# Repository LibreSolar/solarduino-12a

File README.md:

# Solarduino_12A
12A MPPT solar charge controller based on Arduino

Features: 
- 12A MPPT charger
- 55V max PV input
- 12V or 24V battery output
- Arduino-compatible (ATmega 328P used)
- Expandable via break-out of unused ports to standard 2.54 pin-pitch headers (e.g. used for display, communication like CAN/RS485, etc.)

Built-in protection:
- Overvoltage
- Undervoltage
- Overcurrent
- PV short circuit
- PV reverse polarity (for max. module open circuit voltage of around 40V)
- Battery reverse polarity (destructive, fuse is blown)

# Roadmap
- This is the new version of the charge controller. First PCB was sent to production beginning of May 2016. First test results end of May expected.

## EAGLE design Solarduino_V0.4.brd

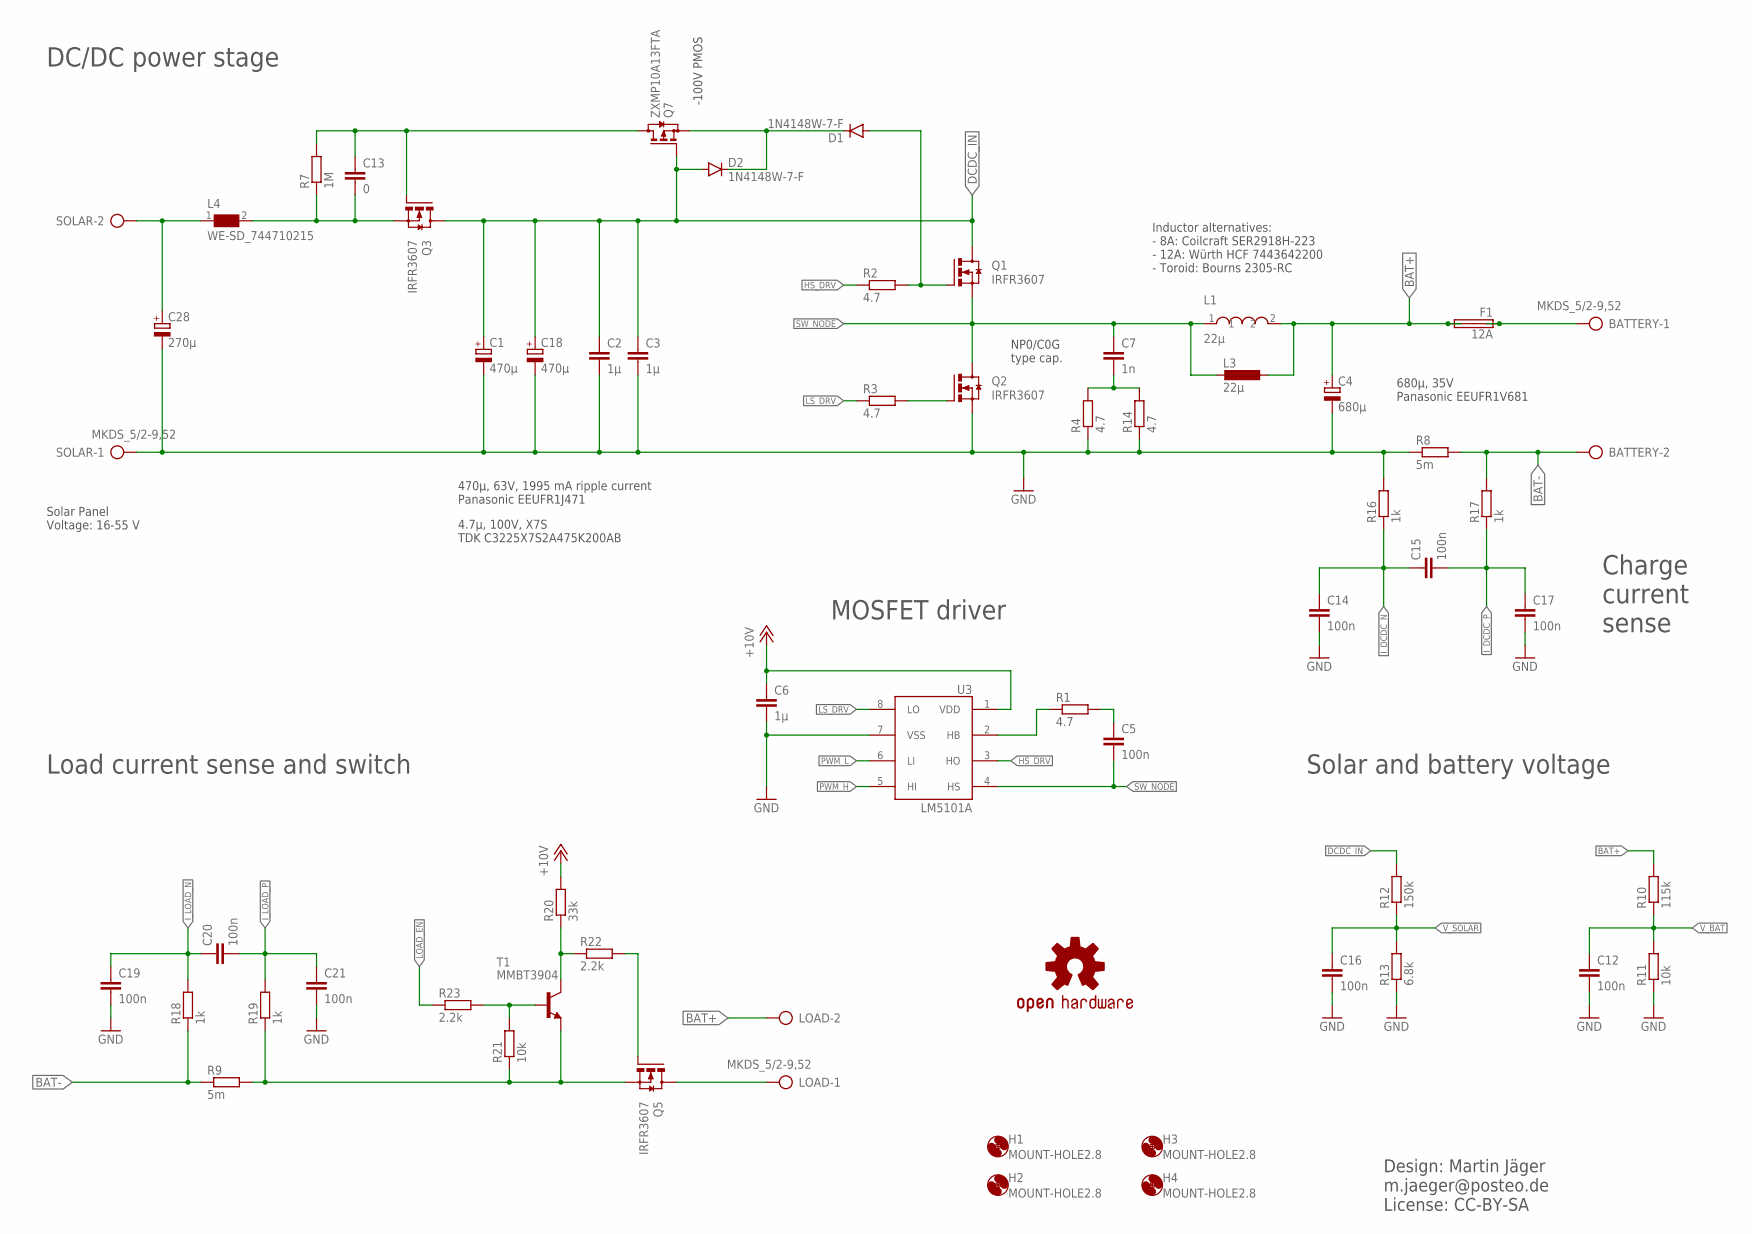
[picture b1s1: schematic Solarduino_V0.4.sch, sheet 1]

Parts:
BATTERY: MKDS_5/2-9,52; MKDS_5/2-952
C1, C18: 470µ; E5-13; MPN EEUFR1J331B
C2, C3: 1µ; C0805; MPN C3225X7S2A475K200AB
C4: 680µ; E5-10,5; MPN EEUFR1E821B
C5, C12, C14, C15, C16, C17, C19, C20, C21: 100n; C0603; MPN 08055C104KAT2A
C6: 1µ; C0603; MPN 08055C104KAT2A
C7: 1n; C0805; MPN 08055C104KAT2A
C13: 0; C0603; MPN 08055C104KAT2A
C28: 270µ; E5-10,5; MPN EEUFR1E821B
D1, D2: 1N4148W-7-F; SOD-123
F1: 12A; BLADE_FUSE_STD
H1, H2, H3, H4: MOUNT-HOLE2.8; 2,8
L1: 22µ; WE-HCF_2818_7443643300; MPN SER2918H-223KL
L3: 22µ; L-BOURNS-2300-H
L4: WE-SD_744710215
LOAD: MKDS_5/2-9,52; MKDS_5/2-952
N1: OSHW-LOGOM; OSHW-LOGO-M
Q1, Q2, Q3, Q5: IRFR3607; DPAK
Q7: ZXMP10A13FTA; SOT23; MPN BSS84-7-F
R1: 4.7; R0805; MPN CR0805-FX-1001ELF
R2, R3: 4.7; R0805; MPN CR0805-FX-1004ELF.
R4, R14: 4.7; R1206; MPN CRM2010-JW-2R2ELF
R7: 1M; R0603; MPN CR0805-FX-1004ELF.
R8, R9: 5m; R2512; MPN CRF2512-FX-R005ELF
R10: 115k; R0603; MPN ERA6AEB104V
R11: 10k; R0603; MPN ERA6AEB682V
R12: 150k; R0603; MPN ERA6AEB104V
R13: 6.8k; R0603; MPN ERA6AEB104V
R16, R17, R18, R19: 1k; R0603; MPN CRM2010-JW-2R2ELF
R20: 33k; R0603; MPN CRM2010-JW-2R2ELF
R21: 10k; R0603; MPN CRM2010-JW-2R2ELF
R22, R23: 2.2k; R0603; MPN CR0805-FX-1004ELF.
SOLAR: MKDS_5/2-9,52; MKDS_5/2-952
T1: MMBT3904; SOT23-BEC
U3: LM5101A; SOIC-8-N

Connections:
+10V: C6.1, R20.2, U3.1 (VDD); also elsewhere on the board
BAT+: C4.+, F1.P$3 (2A), F1.P$4 (2B), L1.2, L3.P$1 (1), LOAD.2, R10.2; also elsewhere on the board
BAT-: BATTERY.2, R8.2, R9.1, R17.2, R18.1
DCDC_IN: C1.+, C2.1, C3.1, C18.+, D2.A, Q1.4 (D), Q3.4 (D), Q7.1 (G), R12.2
FUSE+: BATTERY.1, F1.P$1 (1A), F1.P$2 (1B)
GND: C1.-, C2.2, C3.2, C4.-, C6.2, C12.2, C14.2, C16.2, C17.2, C18.-, C19.2, C21.2, C28.-, Q2.3 (S), R4.1, R8.1, R11.1, R13.1, R14.1, R16.2, SOLAR.1, U3.7 (VSS); also elsewhere on the board
HS_DRV: R2.1, U3.3 (HO)
I_DCDC_N: C14.1, C15.1, R16.1; also elsewhere on the board
I_DCDC_P: C15.2, C17.1, R17.1; also elsewhere on the board
I_LOAD_N: C19.1, C20.1, R18.2; also elsewhere on the board
I_LOAD_P: C20.2, C21.1, R19.2; also elsewhere on the board
LC_OUT: C13.2, L4.2, Q3.3 (S), R7.1
LOAD-: LOAD.1, Q5.4 (D)
LOAD_EN: R23.1; also elsewhere on the board
LOAD_G: Q5.1 (G), R22.2
LS_DRV: R3.1, U3.8 (LO)
unnamed: R1.1, U3.2 (HB)
unnamed: C5.1, R1.2
unnamed: D1.A, Q1.1 (G), R2.2
unnamed: Q5.3 (S), R9.2, R19.1, R21.1, T1.E
unnamed: C13.1, Q3.1 (G), Q7.3 (D), R7.2
unnamed: Q2.1 (G), R3.2
unnamed: D1.C, D2.C, Q7.2 (S)
unnamed: R20.1, R22.1, T1.C
unnamed: C7.2, R4.2, R14.2
unnamed: R21.2, R23.2, T1.B
PWM_H: U3.5 (HI); also elsewhere on the board
PWM_L: U3.6 (LI); also elsewhere on the board
SOLAR+: C28.+, L4.1, SOLAR.2
SW_NODE: C5.2, C7.1, L1.1, L3.P$2 (2), Q1.3 (S), Q2.4 (D), U3.4 (HS)
V_BAT: C12.1, R10.1, R11.2; also elsewhere on the board
V_SOLAR: C16.1, R12.1, R13.2; also elsewhere on the board

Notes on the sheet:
470µ, 63V, 1995 mA ripple current Panasonic EEUFR1J471
680µ, 35V Panasonic EEUFR1V681
Solar Panel Voltage: 16-55 V
Design: Martin Jäger m.jaeger@posteo.de License: CC-BY-SA
DC/DC power stage
4.7µ, 100V, X7S TDK C3225X7S2A475K200AB
Inductor alternatives: - 8A: Coilcraft SER2918H-223 - 12A: Würth HCF 7443642200 - Toroid: Bourns 2305-RC
-100V PMOS
NP0/C0G type cap.
Load current sense and switch
Charge current sense
MOSFET driver
Solar and battery voltage

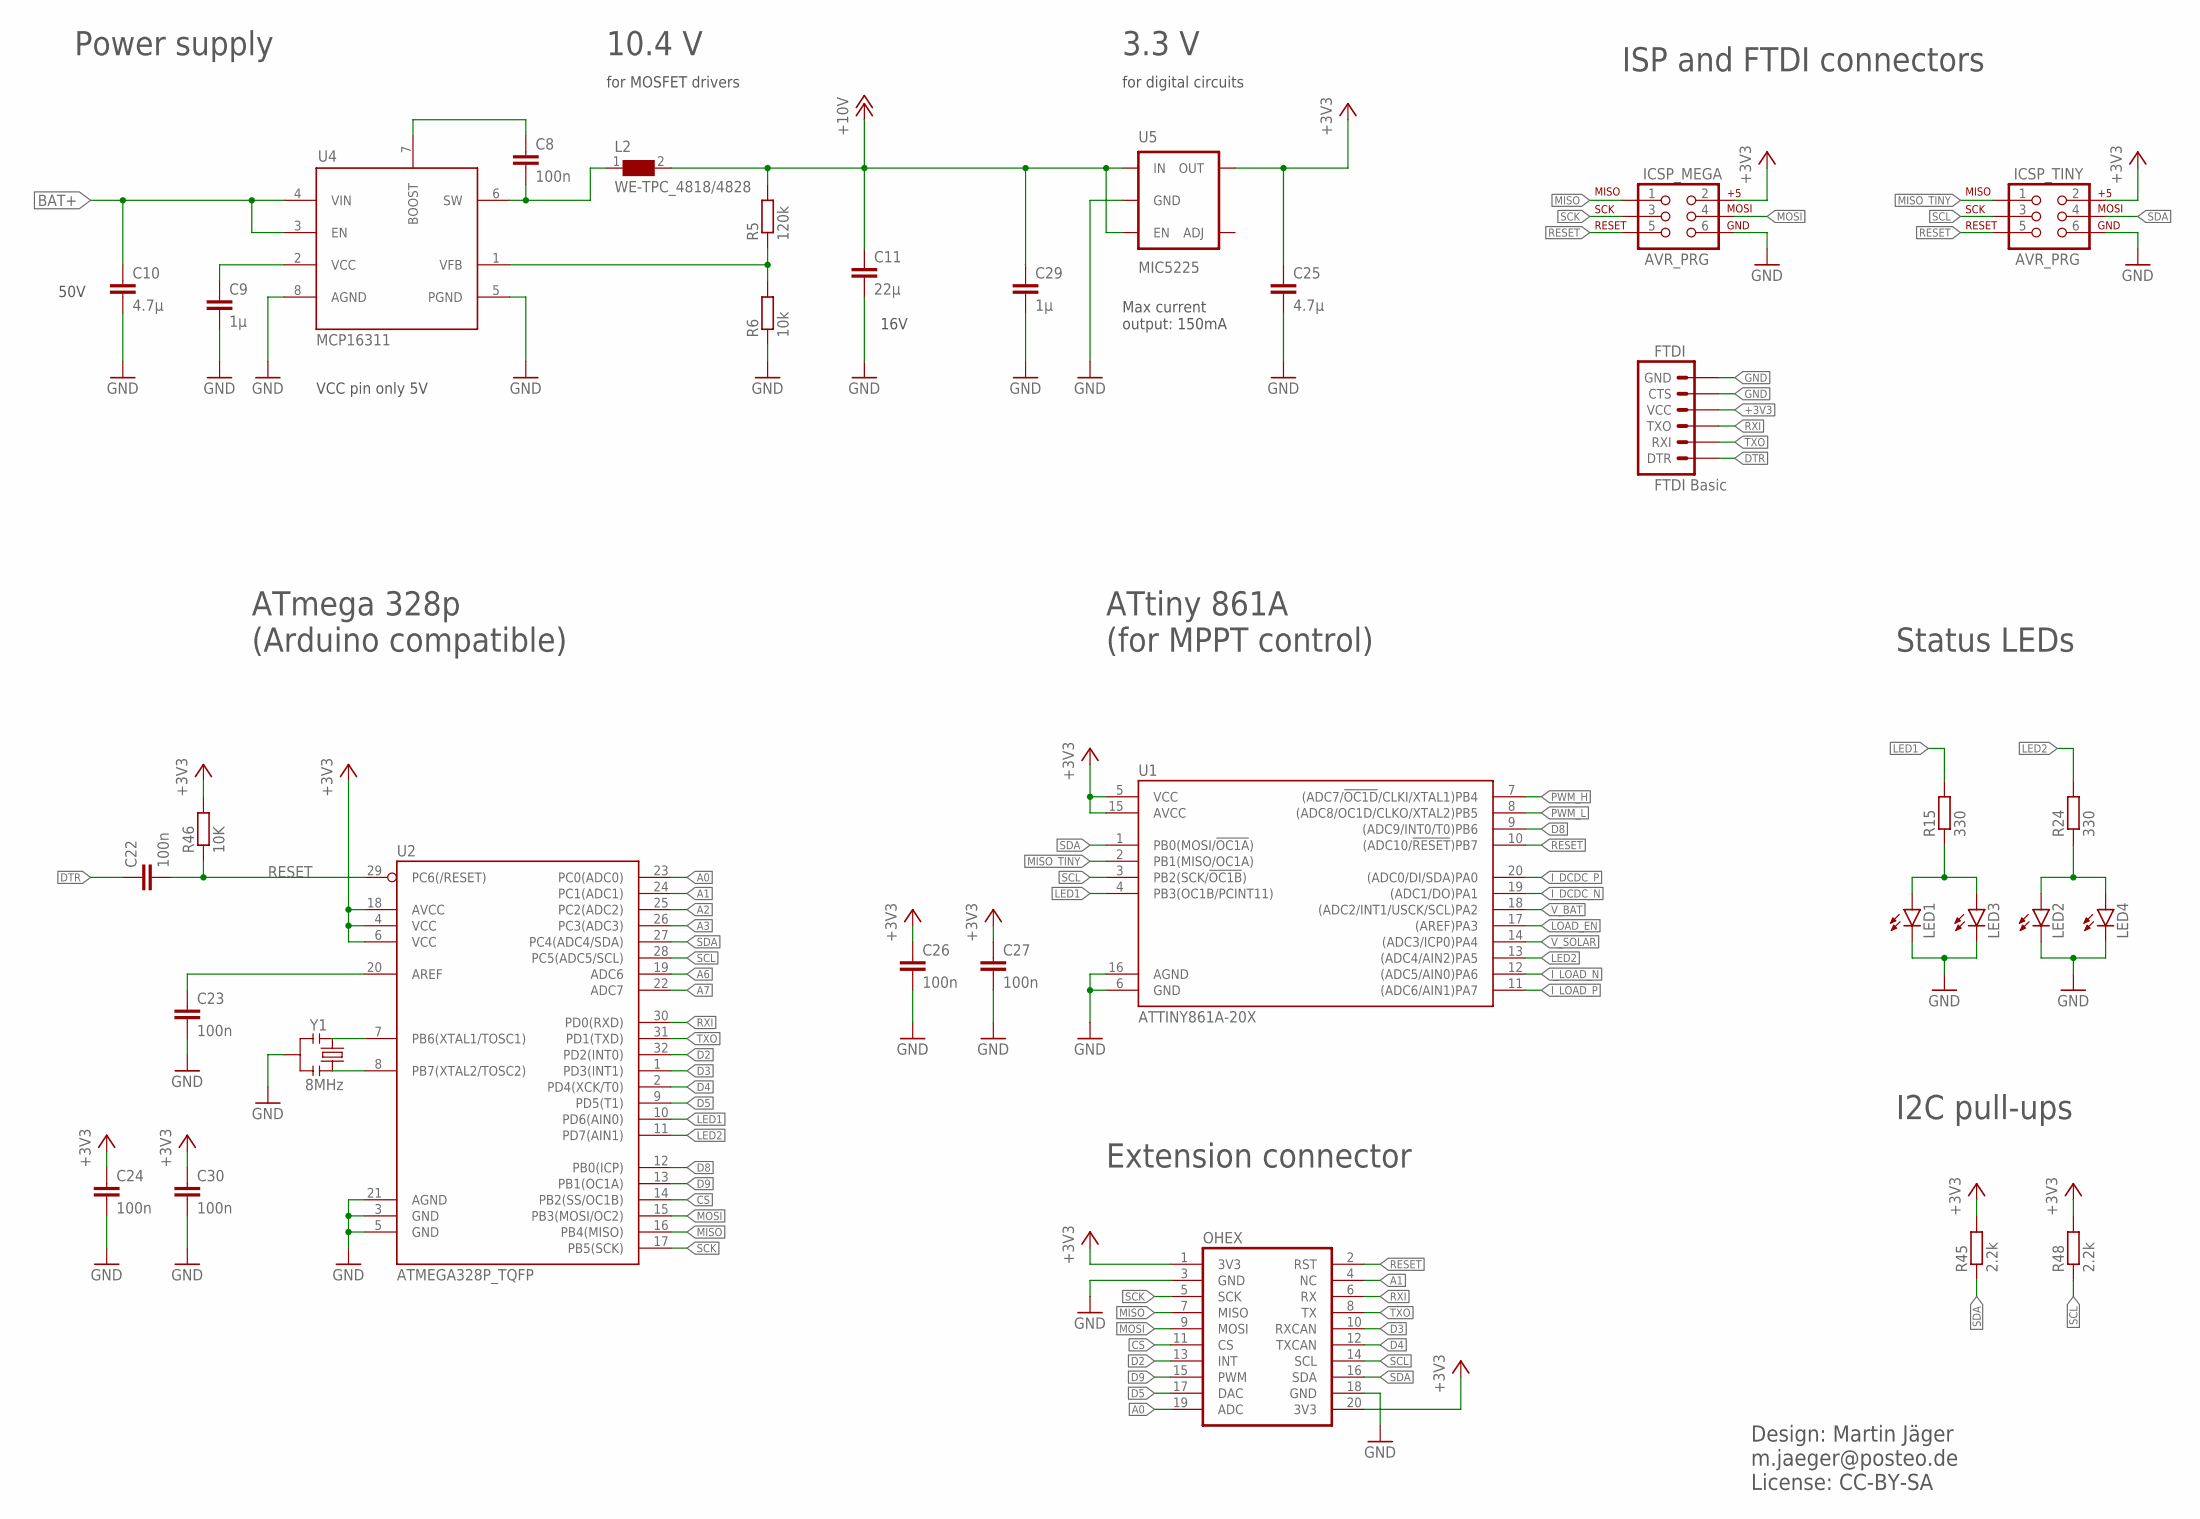
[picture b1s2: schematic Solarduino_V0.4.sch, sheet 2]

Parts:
C8, C22, C23, C24, C26, C27, C30: 100n; C0603; MPN 08055C104KAT2A
C9: 1µ; C0603; MPN 08055C104KAT2A
C10: 4.7µ; C1210; MPN 08055C104KAT2A
C11: 22µ; C1210; MPN 08055C104KAT2A
C25: 4.7µ; C0603; MPN 0805YC475KAT2A
C29: 1µ; C0603; MPN 08053C105KAT2A
FTDI: FTDI Basic; 1X06; MPN 2212S-06SG-85
ICSP_MEGA: AVR_PRG; 2X3
ICSP_TINY: AVR_PRG; 2X3
L2: WE-TPC_4818/4828
LED1, LED2: LED3MM
LED3, LED4: LED0603; LED-0603
OHEX: OHEX; OHEX_SMALL
R5: 120k; R0603; MPN CR0805-FX-1001ELF
R6: 10k; R0603; MPN CR0805-FX-1001ELF
R15, R24: 330; R0603; MPN MCMR06X1001FTL
R45, R48: 2.2k; R0603; MPN CR0805-FX-1001ELF
R46: 10K; R0603; MPN CR0805-FX-1002ELF
U1: ATTINY861A-20X; TSSOP20
U2: ATMEGA328P_TQFP; TQFP32-08
U4: MCP16311; MSOP8
U5: MIC5225; SOT23-5; MPN MIC5225-3.3YM5-TR
Y1: 8MHz; RESONATOR-SMD; MPN CSTCE8M00G55-R0

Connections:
+3V3: C24.1, C25.1, C26.1, C27.1, C30.1, FTDI.4 (VCC), ICSP_MEGA.2, ICSP_TINY.2, OHEX.1 (3V3), OHEX.20 (3V3), R45.2, R46.2, R48.2, U1.5 (VCC), U1.15 (AVCC), U2.4 (VCC), U2.6 (VCC), U2.18 (AVCC), U5.5 (OUT)
+10V: C11.1, C29.1, L2.2, R5.2, U5.1 (IN), U5.3 (EN); also elsewhere on the board
A0: OHEX.19 (ADC), U2.23 (PC0(ADC0))
A1: OHEX.4 (NC), U2.24 (PC1(ADC1))
A2: U2.25 (PC2(ADC2))
A3: U2.26 (PC3(ADC3))
A6: U2.19 (ADC6)
A7: U2.22 (ADC7)
AREF: C23.1, U2.20 (AREF)
BAT+: C10.1, U4.3 (EN), U4.4 (VIN); also elsewhere on the board
CS: OHEX.11 (CS), U2.14 (PB2(SS/OC1B))
D2: OHEX.13 (INT), U2.32 (PD2(INT0))
D3: OHEX.10 (RXCAN), U2.1 (PD3(INT1))
D4: OHEX.12 (TXCAN), U2.2 (PD4(XCK/T0))
D5: OHEX.17 (DAC), U2.9 (PD5(T1))
D8: U1.9 ((ADC9/INT0/T0)PB6), U2.12 (PB0(ICP))
D9: OHEX.15 (PWM), U2.13 (PB1(OC1A))
DTR: C22.1, FTDI.1 (DTR)
GND: C9.2, C10.2, C11.2, C23.2, C24.2, C25.2, C26.2, C27.2, C29.2, C30.2, FTDI.5 (CTS), FTDI.6 (GND), ICSP_MEGA.6, ICSP_TINY.6, LED1.K (C), LED2.K (C), LED3.C, LED4.C, OHEX.3 (GND), OHEX.18 (GND), R6.1, U1.6 (GND), U1.16 (AGND), U2.3 (GND), U2.5 (GND), U2.21 (AGND), U4.5 (PGND), U4.8 (AGND), U5.2 (GND), Y1.2; also elsewhere on the board
I_DCDC_N: U1.19 ((ADC1/DO)PA1); also elsewhere on the board
I_DCDC_P: U1.20 ((ADC0/DI/SDA)PA0); also elsewhere on the board
I_LOAD_N: U1.12 ((ADC5/AIN0)PA6); also elsewhere on the board
I_LOAD_P: U1.11 ((ADC6/AIN1)PA7); also elsewhere on the board
LED1: R15.2, U1.4 (PB3(OC1B/PCINT11)), U2.10 (PD6(AIN0))
LED2: R24.2, U1.13 ((ADC4/AIN2)PA5), U2.11 (PD7(AIN1))
LOAD_EN: U1.17 ((AREF)PA3); also elsewhere on the board
MISO: ICSP_MEGA.1, OHEX.7 (MISO), U2.16 (PB4(MISO))
MISO_TINY: ICSP_TINY.1, U1.2 (PB1(MISO/OC1A))
MOSI: ICSP_MEGA.4, OHEX.9 (MOSI), U2.15 (PB3(MOSI/OC2))
unnamed: C8.2, L2.1, U4.6 (SW)
unnamed: C8.1, U4.7 (BOOST)
unnamed: U2.7 (PB6(XTAL1/TOSC1)), Y1.1
unnamed: C9.1, U4.2 (VCC)
unnamed: U2.8 (PB7(XTAL2/TOSC2)), Y1.3
unnamed: R5.1, R6.2, U4.1 (VFB)
unnamed: LED1.A, LED3.A, R15.1
unnamed: LED2.A, LED4.A, R24.1
PWM_H: U1.7 ((ADC7/!OC1D!/CLKI/XTAL1)PB4); also elsewhere on the board
PWM_L: U1.8 ((ADC8/OC1D/CLKO/XTAL2)PB5); also elsewhere on the board
RESET: C22.2, ICSP_MEGA.5, ICSP_TINY.5, OHEX.2 (RST), R46.1, U1.10 ((ADC10/!RESET!)PB7), U2.29 (PC6(/RESET))
RXI: FTDI.3 (TXO), OHEX.6 (RX), U2.30 (PD0(RXD))
SCK: ICSP_MEGA.3, OHEX.5 (SCK), U2.17 (PB5(SCK))
SCL: ICSP_TINY.3, OHEX.14 (SCL), R48.1, U1.3 (PB2(SCK/!OC1B!)), U2.28 (PC5(ADC5/SCL))
SDA: ICSP_TINY.4, OHEX.16 (SDA), R45.1, U1.1 (PB0(MOSI/!OC1A!)), U2.27 (PC4(ADC4/SDA))
TXO: FTDI.2 (RXI), OHEX.8 (TX), U2.31 (PD1(TXD))
V_BAT: U1.18 ((ADC2/INT1/USCK/SCL)PA2); also elsewhere on the board
V_SOLAR: U1.14 ((ADC3/ICP0)PA4); also elsewhere on the board

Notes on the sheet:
Power supply
Max current output: 150mA
Design: Martin Jäger m.jaeger@posteo.de License: CC-BY-SA
16V
50V
VCC pin only 5V
Status LEDs
ATmega 328p (Arduino compatible)
ATtiny 861A (for MPPT control)
Extension connector
ISP and FTDI connectors
I2C pull-ups
10.4 V
3.3 V
for MOSFET drivers
for digital circuits

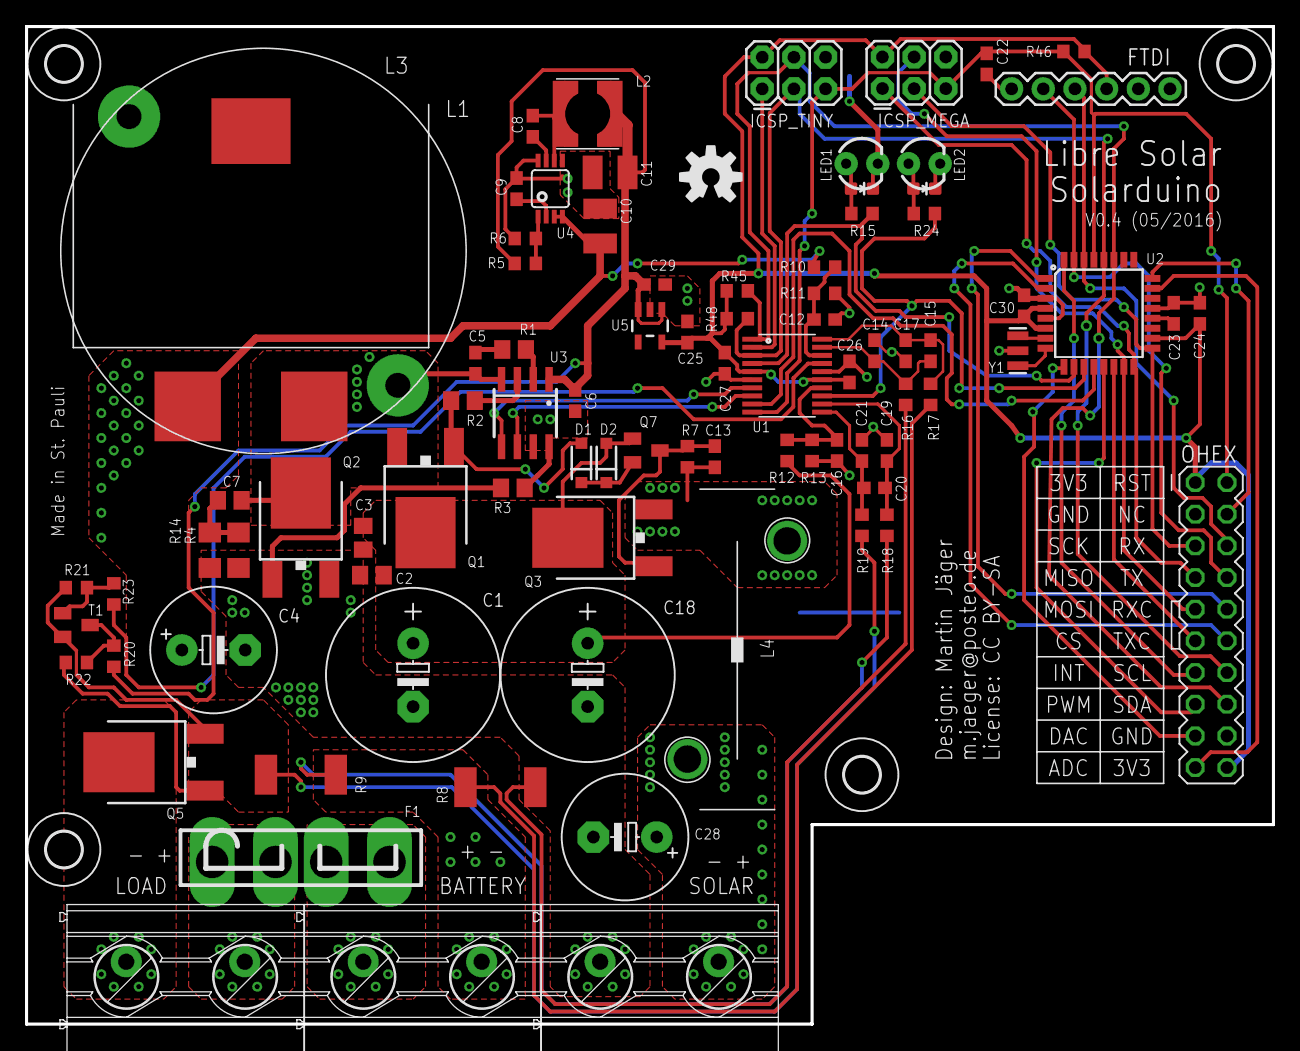
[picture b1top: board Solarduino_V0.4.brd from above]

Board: 2 copper layers, 100.0 x 80.0 mm, 92 parts (0 on the bottom side), 63 nets.

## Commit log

2016-05-06 Initial upload of board to be manufactured by aisler.net
2016-05-06 Added PDF and PNG of schematic and board
2016-05-10 Added some information regarding features

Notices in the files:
parts and their libraries:
SparkFun-Connectors: Licensing: Creative Commons ShareAlike 4.0 International - https://creativecommons.org/licenses/by-sa/4.0
PowerMagnetics: Copyright: Würth Elektronik
